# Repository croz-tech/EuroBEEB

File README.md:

# EuroBEEB
Re-creation of the Control Universal EuroBEEB. EuroBEEB was an Acorn BBC Micro-compatible embedded controller from the early-mid 1980s of the Eurocard format (160mm x 100mm). A standard DIN 41612 bus connector makes the CPU card compatible with the CUBE range of Eurocards.  For a comprehensive background and writeup see https://croz.co.uk/vintage-computer-robot-collection/control-universal-eurobeeb/

# Features
* 6502 CPU
* on-board real-time calendar clock
* a VIA I/O chip providing 16 I/O channels,
4 control lines and 2 timers
* CUBE/ACORN bus
* four reconfigurable 28—pin memory sockets that take RAM or ROM up to 16 kB per device
* choice of memory maps
* battery back-up for the real-time clock and any CMOS RAM on board
* RS-423 serial interface (RS-232 compatible) * RS-422 option for noisy environments
* Auto-run feature allowing Turnkey operation (automatic power-up and run)

# Machine Operating System
The machine operating system used in EuroBEEB provides a software environment similar to that of the BBC Micro and can support BBC BASIC (or other languages) if required. In addition the MOS contains the peripheral drivers (software to drive cards such as the Teletext card) and Control BASIC (an extension of BBC BASIC which provides BASIC-type commands for analog and digital I/O). 

# Evolution
The design is based on the Issue 7 EuroBEEB with a few further improvements:
* Replacement of the IC9/10 PROMs with more readily available GAL16V8 devices
* Addition of an optional pull-up resistor to BUSY+ to avoid modifications at the terminal/BBC
* Option to fit a lithium coin cell in place of the NiMh B1, to avoid leakage risk

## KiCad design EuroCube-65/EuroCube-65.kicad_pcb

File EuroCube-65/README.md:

This folder contains all of the design files in KiCAD 8.
Note that the Gerbers are not published here, but available via the [shared project on PCBWAY](https://www.pcbway.com/project/shareproject/Recreated_Control_Universal_EuroBEEB_900bc94d.html)

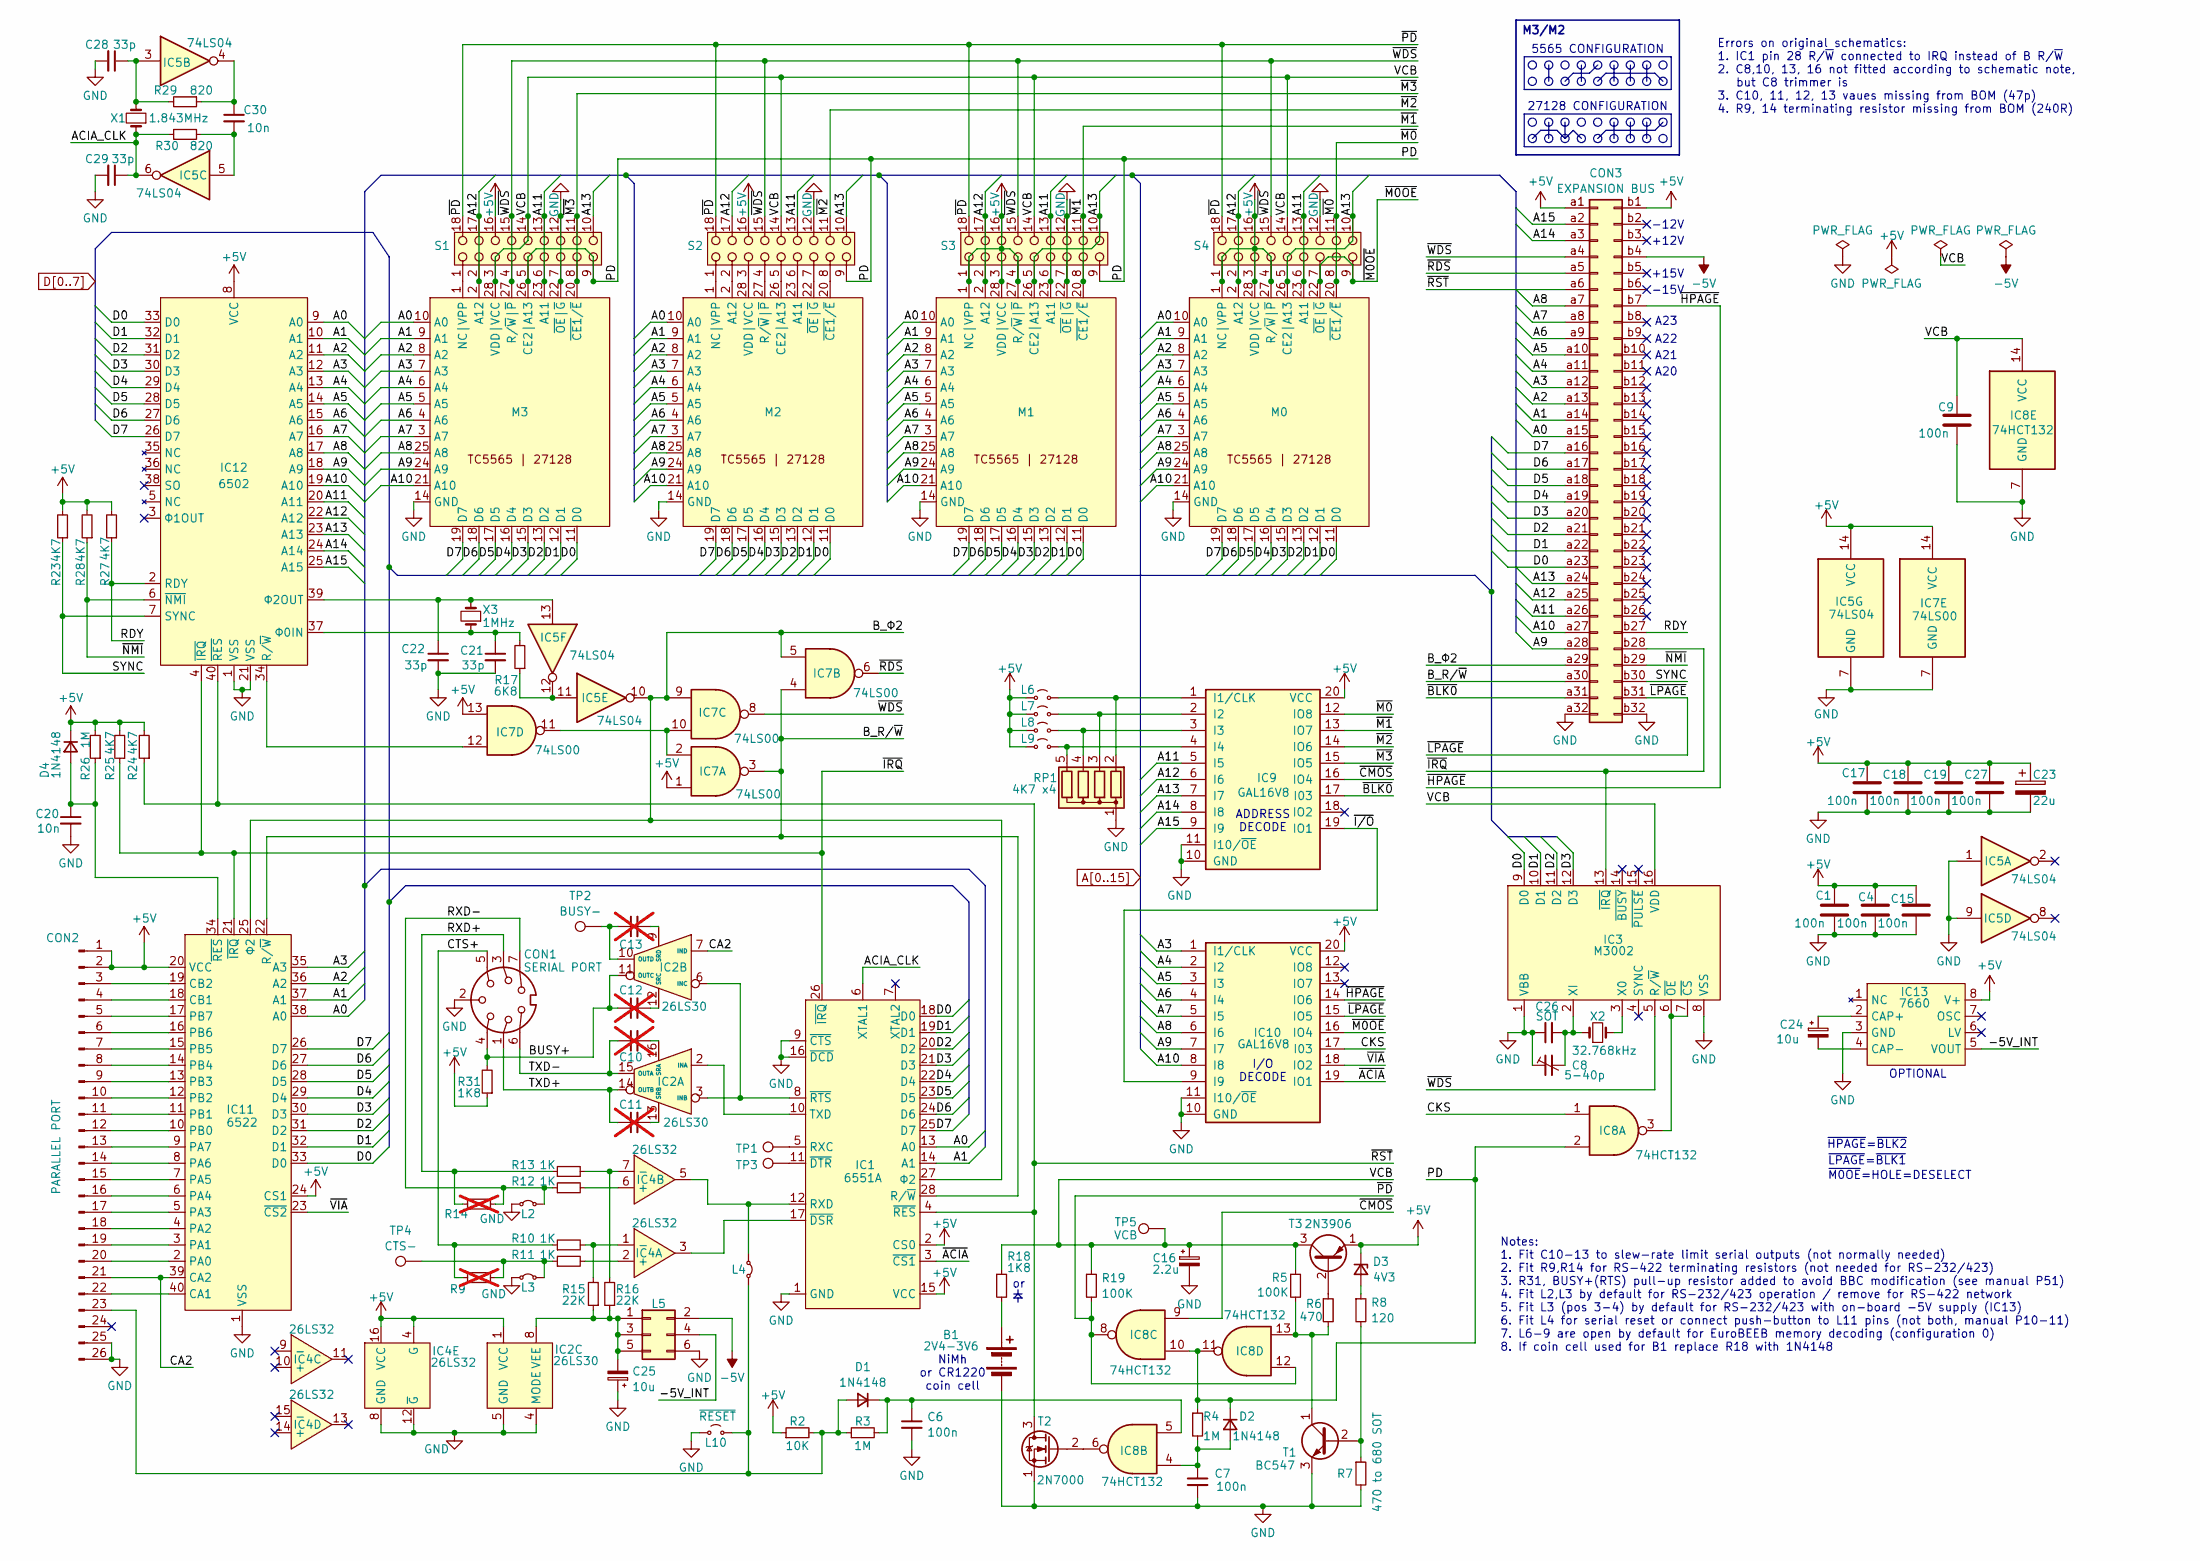
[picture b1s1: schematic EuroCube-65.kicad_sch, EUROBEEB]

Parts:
B1: 2V4-3V6; Battery
C1, C4, C6, C7, C9, C15, C17, C18, C19, C27: 100n; C_Disc_D3.4mm_W2.1mm_P2.50mm
C8: 5-40p; Trimmer_small
C10, C11, C12, C13: 47p; C_Disc_D3.4mm_W2.1mm_P2.50mm; not fitted
C16: 2.2u; CP_Radial_D5.0mm_P2.00mm
C20, C30: 10n; C_Disc_D3.4mm_W2.1mm_P2.50mm
C21, C22, C28, C29: 33p; C_Disc_D3.4mm_W2.1mm_P2.50mm
C23: 22u; CP_Radial_D5.0mm_P2.00mm
C24, C25: 10u; CP_Radial_D5.0mm_P2.00mm
C26: SOT; C_Disc_D3.4mm_W2.1mm_P2.50mm
CON1: SERIAL PORT; DIN-7
CON2: PARALLEL PORT; IDC-Header_2x13-1MP_P2.54mm_Latch_Horizontal
CON3: EXPANSION BUS; DIN41612_B_2x32_Male_Horizontal_THT
D1, D2, D4: 1N4148; D_DO-35_SOD27_P7.62mm_Horizontal
D3: 4V3; D_DO-35_SOD27_P7.62mm_Horizontal
IC1: 6551A; DIP-28_W15.24mm_Socket
IC2: 26LS30; DIP-16_W7.62mm_Socket
IC3: M3002; DIP-16_W7.62mm_Socket
IC4: 26LS32; DIP-16_W7.62mm_Socket
IC5: 74LS04; DIP-14_W7.62mm_Socket
IC7: 74LS00; DIP-14_W7.62mm_Socket
IC8: 74HCT132; DIP-14_W7.62mm_Socket
IC9, IC10: GAL16V8; DIP-20_W7.62mm_Socket
IC11: 6522; DIP-40_W15.24mm_Socket
IC12: 6502; DIP-40_W15.24mm_Socket
IC13: 7660; DIP-8_W7.62mm_Socket
L2, L3, L4, L6, L7, L8, L9: PinHeader_1x02_P2.54mm_V_Tight
L5: PinHeader_2x03_P2.54mm_Vertical
L10: ~{RESET}; PinHeader_1x02_P2.54mm_Vertical
M0, M1, M2, M3: DIP-28_W15.24mm_Socket
R2: 10K; R_Axial_DIN0207_L6.3mm_D2.5mm_P7.62mm_Horizontal
R3, R4, R26: 1M; R_Axial_DIN0207_L6.3mm_D2.5mm_P7.62mm_Horizontal
R5: 100K; R_Axial_DIN0207_L6.3mm_D2.5mm_P7.62mm_Horizontal
R6: 470; R_Axial_DIN0207_L6.3mm_D2.5mm_P7.62mm_Horizontal
R7: 470 to 680 SOT; R_Axial_DIN0207_L6.3mm_D2.5mm_P7.62mm_Horizontal
R8: 120; R_Axial_DIN0207_L6.3mm_D2.5mm_P7.62mm_Horizontal
R9, R14: 240; R_Axial_DIN0207_L6.3mm_D2.5mm_P2.54mm_Vertical; not fitted
R10, R11, R12, R13: 1K; R_Axial_DIN0207_L6.3mm_D2.5mm_P2.54mm_Vertical
R15, R16: 22K; R_Axial_DIN0207_L6.3mm_D2.5mm_P2.54mm_Vertical
R17: 6K8; R_Axial_DIN0207_L6.3mm_D2.5mm_P2.54mm_Vertical
R18, R31: 1K8; R_Axial_DIN0207_L6.3mm_D2.5mm_P2.54mm_Vertical
R19: 100K; R_Axial_DIN0207_L6.3mm_D2.5mm_P2.54mm_Vertical
R23, R28: 4K7; R_Axial_DIN0207_L6.3mm_D2.5mm_P2.54mm_Vertical
R24, R25, R27: 4K7; R_Axial_DIN0207_L6.3mm_D2.5mm_P7.62mm_Horizontal
R29, R30: 820; R_Axial_DIN0207_L6.3mm_D2.5mm_P2.54mm_Vertical
RP1: 4K7 x4; R_Array_SIP5
S1, S3, S4: ConfigBlock_2x09_P2.54mm_Vertical
S2: CERDIP-18_W7.62mm_SideBrazed_Socket
T1: BC547; TO-92_Inline
T2: 2N7000; TO-92_Inline
T3: 2N3906; TO-92_Inline
TP1: RXC; TestPoint_THTPad_D1.5mm_Drill0.7mm
TP2: BUSY-; TestPoint_THTPad_D1.5mm_Drill0.7mm
TP3: ~{DTR}; TestPoint_THTPad_D1.5mm_Drill0.7mm
TP4: CTS-; TestPoint_THTPad_D1.5mm_Drill0.7mm
TP5: VCB; TestPoint_THTPad_D1.5mm_Drill0.7mm
X1: 1.843MHz; Crystal_HC49-U_Vertical
X2: 32.768kHz; Crystal_C38-LF_D3.0mm_L8.0mm_Horizontal
X3: 1MHz; Crystal_HC49-U_Vertical

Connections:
+5V: C1.1, C4.1, C15.1, C17.1, C18.1, C19.1, C23.1, C27.1, CON2.1, CON2.2, CON3.a1, CON3.b1, D3.1 (K), D4.1 (K), IC1.2 (CS0), IC1.15 (VCC), IC2.1 (VCC), IC4.4 (G), IC4.16 (VCC), IC5.14 (VCC), IC7.1, IC7.13, IC7.14 (VCC), IC9.20 (VCC), IC10.20 (VCC), IC11.20 (VCC), IC11.24 (CS1), IC12.8 (VCC), IC13.8 (V+), L6.1 (A), L7.1 (A), L8.1 (A), L9.1 (A), M0.1 (NC|VPP), M0.27 (R/~W|~P), M0.28 (VDD|VCC), M1.1 (NC|VPP), M1.27 (R/~W|~P), M1.28 (VDD|VCC), R2.1, R23.2, R24.2, R25.2, R26.2, R27.2, R28.2, R31.1, S1.16, S2.16, S3.1, S3.3, S3.4, S3.16, S4.1, S4.3, S4.4, S4.16, T3.1 (E)
-5V: CON3.b4, L5.2
/-5V_INT: IC13.5 (VOUT), L5.4
/ACIA_CLK: C29.1, IC1.6 (XTAL1), IC5.6, R30.2, X1.1
/BUSY+: C12.1, CON1.4, IC2.11 (OUTC), R31.2
/B_R/~W: CON3.a30, IC1.28 (R/~W), IC7.3, IC7.4, IC11.22 (R/~W)
/B_Φ2: CON3.a29, IC1.27 (Φ2), IC5.10, IC7.5, IC7.9, IC11.25 (Φ2)
/CA2: CON2.21, IC2.7 (IND), IC11.39 (CA2)
/CKS: IC8.1, IC10.17 (I03)
/CTS+: CON1.5, R9.1, R10.1
/PD: D2.1 (K), IC8.2, IC8.10, IC8.11, M3.26 (CE2|A13), R4.1, S1.5, S1.9, S2.9, S3.9
/RDY: CON3.b27, IC12.2 (RDY), R27.1
/RXD+: CON1.3, R13.1, R14.1
/RXD-: CON1.7, L2.2 (B), R12.1, R14.2
/SYNC: CON3.b30, IC12.7 (SYNC), R23.1
/TXD+: C11.1, CON1.1, IC2.14 (OUTB)
/TXD-: C10.1, CON1.6, IC2.15 (OUTA)
/VCB: C9.1, C16.1, IC3.16 (VDD), IC8.14 (VCC), M3.28 (VDD|VCC), R5.1, R18.1, R19.1, S1.3, S1.14, S2.14, S3.14, S4.14, T3.3 (C), TP5.1
/~ACIA: IC1.3 (~CS1), IC10.19 (IO1)
/~BLK0: CON3.a31, IC9.17 (I03)
/~CMOS: IC8.9, IC9.16 (IO4)
/~HPAGE: CON3.b7, IC10.14 (IO6)
/~IRQ: CON3.b28, IC1.26 (~IRQ), IC3.13 (~IRQ), IC11.21 (~IRQ), IC12.4 (~IRQ), R25.1
/~I/O: IC9.19 (IO1), IC10.9 (I9)
/~LPAGE: CON3.b31, IC10.15 (IO5)
/~M0OE: IC10.16 (IO4), M0.22 (~OE|~G), S4.7, S4.9
/~M0: IC9.12 (IO8), M0.20 (~CE1/~E), S4.8, S4.11
/~M1: IC9.13 (IO7), M1.20 (~CE1/~E), S3.8, S3.11
/~M2: IC9.14 (IO6), S2.11
/~M3: IC9.15 (IO5), M3.20 (~CE1/~E), S1.8, S1.11
/~NMI: CON3.b29, IC12.6 (~NMI), R28.1
/~PD: IC8.8, IC8.12, R19.2, S1.18, S2.18, S3.18, S4.18
/~RDS: CON3.a5, IC7.6
/~RST: CON3.a6, IC1.4 (~RES), IC12.40 (~RES), R24.1, T2.3 (D)
/~VIA: IC10.18 (IO2), IC11.23 (~CS2)
/~WDS: CON3.a4, IC3.5 (R/~W), IC7.8, M3.27 (R/~W|~P), S1.4, S1.15, S2.15, S3.15, S4.15
A0: CON3.a15, IC1.13 (A0), IC11.38 (A0), IC12.9 (A0), M0.10 (A0), M1.10 (A0), M2.10 (A0), M3.10 (A0)
A1: CON3.a14, IC1.14 (A1), IC11.37 (A1), IC12.10 (A1), M0.9 (A1), M1.9 (A1), M2.9 (A1), M3.9 (A1)
A2: CON3.a13, IC11.36 (A2), IC12.11 (A2), M0.8 (A2), M1.8 (A2), M2.8 (A2), M3.8 (A2)
A3: CON3.a12, IC10.1 (I1/CLK), IC11.35 (A3), IC12.12 (A3), M0.7 (A3), M1.7 (A3), M2.7 (A3), M3.7 (A3)
A4: CON3.a11, IC10.2 (I2), IC12.13 (A4), M0.6 (A4), M1.6 (A4), M2.6 (A4), M3.6 (A4)
A5: CON3.a10, IC10.3 (I3), IC12.14 (A5), M0.5 (A5), M1.5 (A5), M2.5 (A5), M3.5 (A5)
A6: CON3.a9, IC10.4 (I4), IC12.15 (A6), M0.4 (A6), M1.4 (A6), M2.4 (A6), M3.4 (A6)
A7: CON3.a8, IC10.5 (I5), IC12.16 (A7), M0.3 (A7), M1.3 (A7), M2.3 (A7), M3.3 (A7)
A8: CON3.a7, IC10.6 (I6), IC12.17 (A8), M0.25 (A8), M1.25 (A8), M2.25 (A8), M3.25 (A8)
A9: CON3.a28, IC10.7 (I7), IC12.18 (A9), M0.24 (A9), M1.24 (A9), M2.24 (A9), M3.24 (A9)
A10: CON3.a27, IC10.8 (I8), IC12.19 (A10), M0.21 (A10), M1.21 (A10), M2.21 (A10), M3.21 (A10)
A11: CON3.a26, IC9.5 (I5), IC12.20 (A11), M0.23 (A11), M1.23 (A11), M3.23 (A11), S1.6, S1.13, S2.13, S3.6, S3.13, S4.6, S4.13
A12: CON3.a25, IC9.6 (I6), IC12.22 (A12), M0.2 (A12), M1.2 (A12), M3.2 (A12), S1.2, S1.17, S2.17, S3.2, S3.17, S4.2, S4.17
A13: CON3.a24, IC9.7 (I7), IC12.23 (A13), M0.26 (CE2|A13), M1.26 (CE2|A13), S1.10, S2.10, S3.5, S3.10, S4.5, S4.10
A14: CON3.a3, IC9.8 (I8), IC12.24 (A14)
A15: CON3.a2, IC9.9 (I9), IC12.25 (A15)
D0: CON3.a23, IC1.18 (D0), IC3.9 (D0), IC11.33 (D0), IC12.33 (D0), M0.11 (D0), M1.11 (D0), M2.11 (D0), M3.11 (D0)
D1: CON3.a22, IC1.19 (D1), IC3.10 (D1), IC11.32 (D1), IC12.32 (D1), M0.12 (D1), M1.12 (D1), M2.12 (D1), M3.12 (D1)
D2: CON3.a21, IC1.20 (D2), IC3.11 (D2), IC11.31 (D2), IC12.31 (D2), M0.13 (D2), M1.13 (D2), M2.13 (D2), M3.13 (D2)
D3: CON3.a20, IC1.21 (D3), IC3.12 (D3), IC11.30 (D3), IC12.30 (D3), M0.15 (D3), M1.15 (D3), M2.15 (D3), M3.15 (D3)
D4: CON3.a19, IC1.22 (D4), IC11.29 (D4), IC12.29 (D4), M0.16 (D4), M1.16 (D4), M2.16 (D4), M3.16 (D4)
D5: CON3.a18, IC1.23 (D5), IC11.28 (D5), IC12.28 (D5), M0.17 (D5), M1.17 (D5), M2.17 (D5), M3.17 (D5)
D6: CON3.a17, IC1.24 (D6), IC11.27 (D6), IC12.27 (D6), M0.18 (D6), M1.18 (D6), M2.18 (D6), M3.18 (D6)
D7: CON3.a16, IC1.25 (D7), IC11.26 (D7), IC12.26 (D7), M0.19 (D7), M1.19 (D7), M2.19 (D7), M3.19 (D7)
GND: B1.2 (-), C1.2, C4.2, C6.2, C7.2, C8.1, C9.2, C15.2, C16.2, C17.2, C18.2, C19.2, C20.2, C21.2, C22.2, C23.2, C25.1, C26.1, C27.2, C28.2, C29.2, CON1.2, CON2.25, CON2.26, CON3.a32, CON3.b32, IC1.1 (GND), IC1.9 (~CTS), IC1.16 (~DCD), IC2.4 (MODE), IC2.5 (GND), IC3.1 (VBB), IC3.8 (VSS), IC4.8 (GND), IC4.12 (~G), IC5.1, IC5.7 (GND), IC5.9, IC7.7 (GND), IC8.7 (GND), IC9.10 (GND), IC9.11 (I10/~OE), IC10.10 (GND), IC10.11 (I10/~OE), IC11.1 (VSS), IC12.1 (VSS), IC12.21 (VSS), IC13.3 (GND), L2.1 (A), L3.1 (A), L5.6, L10.1 (A), M0.14 (GND), M1.14 (GND), M1.22 (~OE|~G), M2.14 (GND), M3.14 (GND), M3.22 (~OE|~G), R7.2, RP1.1 (common), S1.7, S1.12, S2.12, S3.7, S3.12, S4.12, T1.3 (E), T2.1 (S)
unnamed: B1.1 (+), R18.2
unnamed: C28.1, IC5.3, R29.2, X1.2
unnamed: C30.1, IC5.4, R29.1
unnamed: C30.2, IC5.5, R30.1
unnamed: CON2.3, IC11.19 (CB2)
unnamed: CON2.4, IC11.18 (CB1)
unnamed: CON2.5, IC11.17 (PB7)
unnamed: CON2.6, IC11.16 (PB6)
unnamed: CON2.7, IC11.15 (PB5)
unnamed: CON2.8, IC11.14 (PB4)
unnamed: CON2.9, IC11.13 (PB3)
unnamed: CON2.10, IC11.12 (PB2)
unnamed: CON2.11, IC11.11 (PB1)
unnamed: CON2.12, IC11.10 (PB0)
unnamed: CON2.13, IC11.9 (PA7)
unnamed: CON2.14, IC11.8 (PA6)
unnamed: CON2.15, IC11.7 (PA5)
unnamed: CON2.16, IC11.6 (PA4)
unnamed: CON2.17, IC11.5 (PA3)
unnamed: CON2.18, IC11.4 (PA2)
unnamed: CON2.19, IC11.3 (PA1)
unnamed: CON2.20, IC11.2 (PA0)
unnamed: CON2.22, IC11.40 (CA1)
unnamed: CON2.23, D1.2 (A), L4.2 (B), L10.2 (B), R2.2, R3.1
unnamed: C6.1, D1.1 (K), IC8.5, R3.2
unnamed: C7.1, D2.2 (A), IC8.4, R4.2
unnamed: D3.2 (A), R8.1
unnamed: C20.1, D4.2 (A), IC11.34 (~RES), R26.1
unnamed: IC1.5 (RXC), TP1.1
unnamed: IC1.12 (RXD), IC4.5, L4.1 (A)
unnamed: IC1.10 (TXD), IC2.2 (INA)
unnamed: IC1.17 (~DSR), IC4.3
unnamed: IC1.11 (~DTR), TP3.1
unnamed: IC1.8 (~RTS), IC2.3 (INB), IC2.6 (INC)
unnamed: C10.2, IC2.16 (SRA)
unnamed: C11.2, IC2.13 (SRB)
unnamed: C13.1, IC2.10 (OUTD), TP2.1
unnamed: C12.2, IC2.12 (SRC)
unnamed: C13.2, IC2.9 (SRD)
unnamed: C25.2, IC2.8 (VEE), L5.1, L5.3, L5.5, R15.1, R16.1
unnamed: IC3.3 (X0), X2.2
unnamed: C8.2, C26.2, IC3.2 (XI), X2.1
unnamed: IC3.6 (~OE), IC3.7 (~CS), IC8.3
unnamed: IC4.2 (+), R11.2
unnamed: IC4.1 (-), R10.2, R15.2
unnamed: IC4.6 (+), R12.2
unnamed: IC4.7 (-), R13.2, R16.2
unnamed: IC5.11, IC5.12, R17.1
unnamed: IC7.2, IC7.10, IC7.11
unnamed: IC9.1 (I1/CLK), L6.2 (B), RP1.2 (R1)
unnamed: IC9.2 (I2), L7.2 (B), RP1.3 (R2)
unnamed: IC9.3 (I3), L8.2 (B), RP1.4 (R3)
unnamed: IC9.4 (I4), L9.2 (B), RP1.5 (R4)
unnamed: IC7.12, IC12.34 (R/~W)
unnamed: C21.1, IC12.37 (Φ0IN), R17.2, X3.1
unnamed: C22.1, IC5.13, IC12.39 (Φ2OUT), X3.2
unnamed: C24.1, IC13.2 (CAP+)
unnamed: C24.2, IC13.4 (CAP-)
unnamed: L3.2 (B), R9.2, R11.1, TP4.1
unnamed: M2.23 (A11), S2.6
unnamed: M2.2 (A12), S2.2
unnamed: M2.26 (CE2|A13), S2.5
unnamed: M2.1 (NC|VPP), S2.1
unnamed: M2.27 (R/~W|~P), S2.4
unnamed: M2.28 (VDD|VCC), S2.3
unnamed: M2.20 (~CE1/~E), S2.8
unnamed: M2.22 (~OE|~G), S2.7
unnamed: M3.1 (NC|VPP), S1.1
unnamed: R7.1, R8.2, T1.2 (B)
unnamed: IC8.13, R5.2, R6.2, T1.1 (C)
unnamed: IC8.6, T2.2 (G)
unnamed: R6.1, T3.2 (B)

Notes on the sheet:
~{LPAGE}=~{BLK1}
~{HPAGE}=~{BLK2}
OPTIONAL
A20
-15V
A22
A23
-12V
+15V
I/O DECODE
NiMh or CR1220 coin cell
ADDRESS DECODE
A21
5565 CONFIGURATION
~{M0OE}=HOLE=DESELECT
27128 CONFIGURATION
+12V
Errors on original schematics: 1. IC1 pin 28 R/~{W} connected to IRQ instead of B R/~{W} 2. C8,10, 13, 16 not fitted according to schematic note, but C8 trimmer is 3. C10, 11, 12, 13 vaues missing from BOM (47p) 4. R9, 14 terminating resistor missing from BOM (240R)
M3/M2
Notes: 1. Fit C10-13 to slew-rate limit serial outputs (not normally needed) 2. Fit R9,R14 for RS-422 terminating resistors (not needed for RS-232/423) 3. R31, BUSY+(RTS) pull-up resistor added to avoid BBC modification (see manual P51) 4. Fit L2,L3 by default for RS-232/423 operation / remove for 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

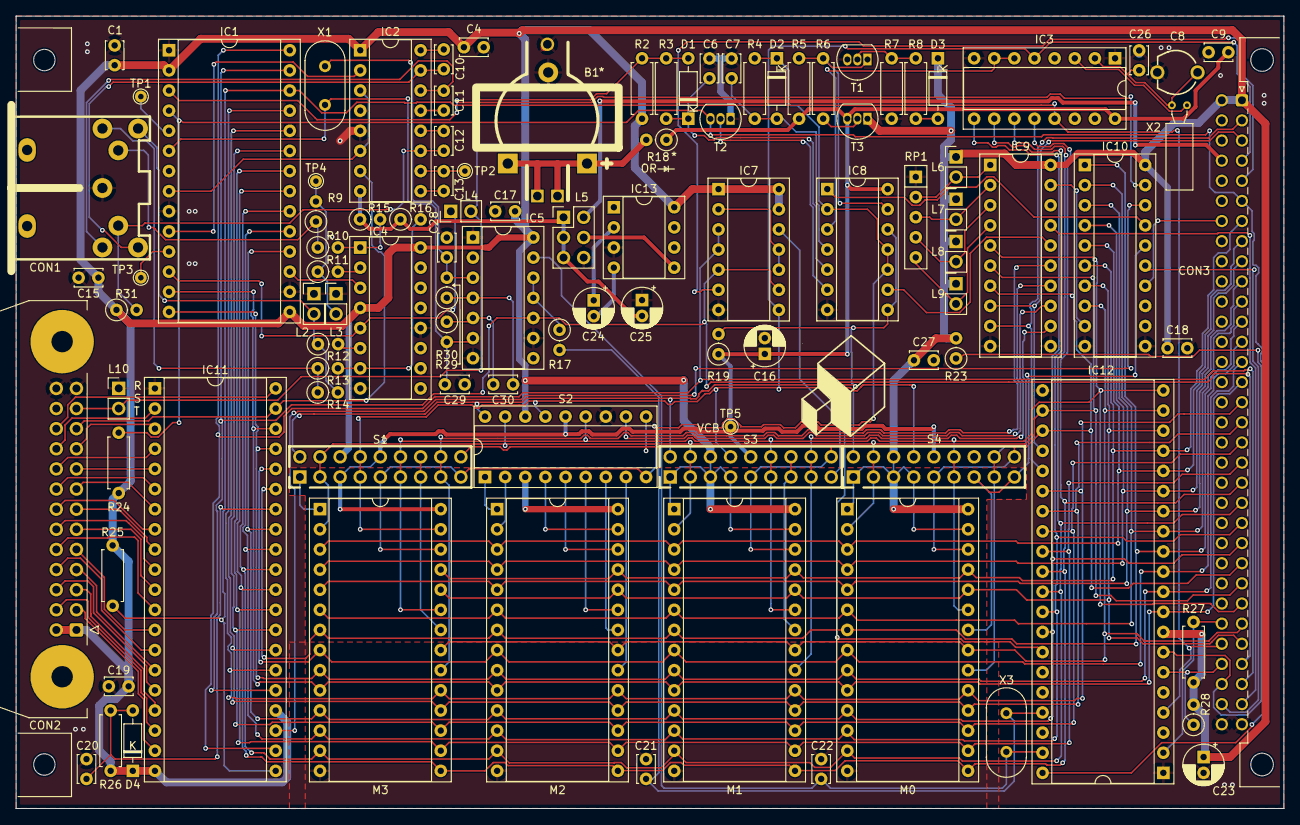
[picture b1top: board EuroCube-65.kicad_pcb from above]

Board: 2 copper layers, 160.0 x 100.0 mm, 104 parts (0 on the bottom side), 133 nets.

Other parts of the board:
H1, H2: MountingHole; MountingHole_2.7mm_M2.5

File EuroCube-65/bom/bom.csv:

"Reference","Value","Qty","DNP","Source"
"B1","2V4-3V6","1","","NiMh: https://www.ebay.com/itm/303608055779 or CR1220 coin cell (https://a.co/d/0sKtg3F) and holder (https://mou.sr/4iOCzqd)"
"C1,C4,C6,C7,C9,C15,C17,C18,C19,C27","100n","10","","Mouser https://mou.sr/3VUTNs3"
"C8","5-40p","1","","(or 5-30pF) must be small footprint e.g. Anchor Electronics https://anchor-electronics.com/price-list.pdf"
"C10,C11,C12,C13","47p","4","DNP","Mouser https://mou.sr/4iUAKb8"
"C16","2.2u","1","","Mouser https://mou.sr/4iWQR84"
"C20,C30","10n","2","","Mouser https://mou.sr/3O75zLF"
"C21,C22,C28,C29","33p","4","","Use 13pF matched to crystals linked below, Mouser https://mou.sr/4a27NpB"
"C23","22u","1","","Mouser https://mou.sr/3DLIpZ6"
"C24,C25","10u","2","","Mouser https://mou.sr/3BQdcDy"
"C26","SOT","1","",""
"CON1","SERIAL PORT","1","","DIN-7 ebay example: https://www.ebay.com/itm/254570069647"
"CON2","PARALLEL PORT","1","","26W Latching RA header, male, long latches, Anchor Electronics https://anchor-electronics.com/price-list.pdf"
"CON3","EXPANSION BUS","1","","DIN 41612, 2 row, 64 pos, male, RA, Mouser https://mou.sr/4aexeVj"
"D1,D2,D4","1N4148","3","","Mouser https://mou.sr/3wZtszk (plus one extra if using a coin cell for battery backup)"
"D3","4V3","1","","Mouser https://mou.sr/4fJod7r"
"IC1","6551A","1","","Ebay, example: https://www.ebay.com/itm/254521312074"
"IC2","26LS30","1","","Anchor Electronics https://anchor-electronics.com/price-list.pdf"
"IC3","M3002","1","","Ebay, example: https://www.ebay.com/itm/226476043911"
"IC4","26LS32","1","","Mouser https://mou.sr/420G8TU"
"IC5","74LS04","1","","Mouser https://mou.sr/3TKMrV4"
"IC7","74LS00","1","","Mouser https://mou.sr/3w5Mdxk"
"IC8","74HCT132","1","","Mouser https://mou.sr/4gUzrHh"
"IC9,IC10","GAL16V8","2","","Ebay, example: https://www.ebay.com/itm/363965912636"
"IC11","6522","1","","Ebay, example: https://www.ebay.com/itm/145848493201"
"IC12","6502","1","","Ebay, example: https://www.ebay.com/itm/405284509359"
"IC13","7660","1","","Mouser https://mou.sr/4iOD8jP"
"L2,L3,L4,L5,L6,L7,L8,L9,M0,M1,M2,M3,S1,S2,S3,S4","~","16","","0.1"" pin headers / for S2 use https://www.digikey.com/short/ptm1q42r and https://www.digikey.com/short/j0rtv0z3 , for M2/M3 use https://www.ebay.com/itm/224690436829"
"L10","~{RESET}","1","","0.1"" pin header"
"R2","10K","1","","Mouser https://mou.sr/40g8pVm"
"R3,R4,R26","1M","3","","Mouser https://mou.sr/4fHA8mv"
"R5,R19","100K","2","","Mouser https://mou.sr/3DDC2XZ"
"R6","470","1","","Mouser https://mou.sr/3PjO638"
"R7","470 to 680 SOT","1","","e.g. 470R Mouser https://mou.sr/3PjO638"
"R8","120","1","","Mouser https://mou.sr/3BGw6gi"
"R9,R14","240","2","DNP","Mouser https://mou.sr/4gSpnyA"
"R10,R11,R12,R13","1K","4","","Mouser https://mou.sr/3S4nkwA"
"R15,R16","22K","2","","Mouser https://mou.sr/3BFqHWN"
"R17","6K8","1","","Mouser https://mou.sr/4gAKzt4"
"R18,R31","1K8","2","","Mouser https://mou.sr/4gzF7GX"
"R23,R24,R25,R27,R28","4K7","5","","Mouser https://mou.sr/4gFZO4k"
"R29,R30","820","2","","Mouser https://mou.sr/4j0kbdN"
"RP1","4K7 x4","1","","Mouser https://mou.sr/4fGkWG9"
"T1","BC547","1","","Mouser https://mou.sr/3Dz5VIR"
"T2","2N7000","1","","Mouser https://mou.sr/47xjkvW"
"T3","2N3906","1","","Mouser https://mou.sr/4gzFu4j"
"TP1","RXC","1","",""
"TP3","~{DTR}","1","",""
"X1","1.843MHz","1","","Mouser https://mou.sr/3PeAg1M"
"X2","32.768kHz","1","","Anchor Electronics https://anchor-electronics.com/price-list.pdf"
"X3","1MHz","1","","Mouser https://mou.sr/3PdVQDI"

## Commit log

2024-12-23 Fist update
2024-12-24 added ROMs
2024-12-24 Added datasheets
2024-12-24 Added 2N3906
2024-12-24 Added 2N7000
2024-12-24 Added BC547
2024-12-24 Added 7660
2024-12-24 Added M3002
2024-12-24 Added 5565
2024-12-24 Update sch
2024-12-24 Added manual
2024-12-24 Minor updates to schematic/BOM
2024-12-25 Added footprints, started laying out
2024-12-26 All laid out, ready to route
2024-12-26 Update gitignore
2024-12-28 First track layout
2024-12-28 Finished layout
    Added coin cell option
    Added logo
    Added label, issue, contacts to rear
2024-12-28 Fixed bus connector location
2024-12-28 Added filled zones
2024-12-29 Tidying of unnecessary GND traces
2024-12-29 Minor footprint tweaks
2025-01-04 Updated typo, added bom/ibom
2025-01-04 Updated ibom to blacklist/remove unpopulated parts
2025-01-05 Added the HardwareDebug contents
2025-01-06 Added files for the GALs
2025-01-06 Added address decoder tester
    This uses an Arduino Mega and runs through all possible 16bit memory space addresses to the GAL(s) while monitoring the decoded outputs and writing to the serial debug to create a visual memory map.
2025-01-12 Updated decode tester, labels, ROM and samples.ssd
    - Updated the memory address decode tester to fix the last address
    - Added the label files for use with Dymo MobileLabeller
    - Added the EURO414 ROM for the BBC Micro
    - Added the SSD containing the sample / test BASIC programs
2025-01-12 Updated BOM with correct battery references
2025-01-12 Update README.md with link to website
2025-01-12 Update README.md with image
2025-01-12 Typo in README.md fixed
2025-01-12 Added link to PCBway project
2025-01-12 Added automos disk image
2025-01-20 Added more labels
    Note that the 28C256 labels are for EEPROMS, which must be programmed into the top half (from 0x4000)
2025-01-21 Rolled back to working versions (V2)
    Note that these ignore L6..L9 and only do the memory decode for the EuroBEEB at this time
2025-02-18 IC9 GAL files updated to decode all maps
    All maps now decoded -
    9a files decode maps 0x0-0x9 << use this one for EuroBEEB
    9b files decode maps 0xA-0xE
2025-03-25 Fixed typos on note 5 and 6
    Fixed the typos on notes 5 and 6 referring to the incorrect link numbers
